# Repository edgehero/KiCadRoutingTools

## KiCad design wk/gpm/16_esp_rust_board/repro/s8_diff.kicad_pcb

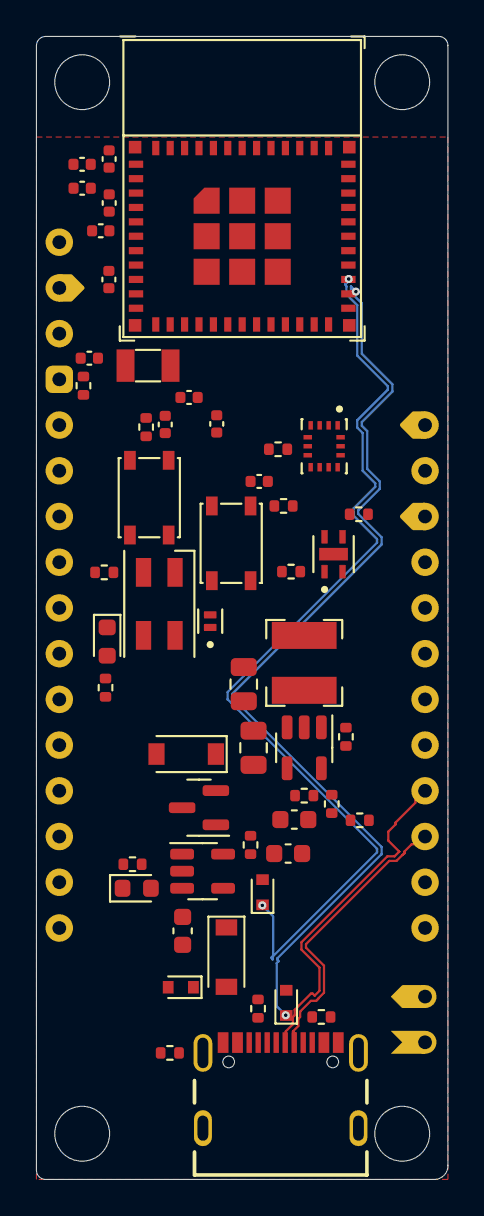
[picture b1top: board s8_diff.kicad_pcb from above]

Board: 2 copper layers, 22.9 x 63.5 mm, 55 parts (1 on the bottom side), 35 nets.

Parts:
C1, C2, C11: 10nF 10V; C_0402_1005Metric
C3, C4, C9: 100nF 10V; C_0402_1005Metric
C5, C7: 10uF 16V; C_0805_2012Metric
C6: 22pF 50V; C_0603_1608Metric
C8, C10: 1uF 16V; C_0402_1005Metric
C12, C13: DNP; C_0402_1005Metric
C14: 1nF 10V; C_0402_1005Metric
C15, C16: 4.7uF 16V; C_0603_1608Metric
D1: LESD8D3.3CAT5G; SOD-882
D2, D3: LED; LED_0603_1608Metric
D4, D6: B5819W; D_SOD-123
D5, D7, D8: LESD5D5.0CT1G; D_SOD-523
D9: WS2812B; LED_SK6812MINI_PLCC4_3.5x3.5mm_P1.75mm
J1: USB4105-GF-A; GCT_USB4105-GF-A
L1: SPH4018H2R2MT (2.2uH 2.2A); L_Bourns-SRN4018
Q1: DMG3415U; SOT-23
R1, R8, R9, R17, R18, R19: 10kR 1%; R_0402_1005Metric
R2, R15: 100kR 1%; R_0402_1005Metric
R3: 22k1R 1%; R_0402_1005Metric
R4, R6: 5k1R 1%; R_0402_1005Metric
R5, R7, R11: 0R 1%; R_0402_1005Metric
R10: 470R 1%; R_0402_1005Metric
R12: DNP; R_0402_1005Metric
R14: 1kR 1%; R_0402_1005Metric
SW1, SW2: SW_Push; SW_SPST_PTS810
TP2: IMU_INT2; TestPoint_Pad_D1.0mm
U1: SHTC3; SON100P200X200X80-5N
U2: ICM-42670-P; IC_ICM-42670-P
U3: ESP32-C3-MINI-1
U4: Rust_Board
U5: SY8088; SOT-23-5
U6: MCP73831T-2ACI/OT; SOT-23-5
Y1: 32.768Hz; Crystal_SMD_3215-2Pin_3.2x1.5mm

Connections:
+3V3: C1.1, C2.1, C3.1, C4.1, C6.1, C7.1, C8.1, C9.1, C11.1, D1.1 (A1), D9.1 (VDD), L1.2, R2.1, R7.2, R8.1, R17.1, R18.1, R19.1, U1.1 (VDD), U2.5 (VDDIO), U2.8 (VDD), U3.3 (3V3), U4.2 (3V3)
+5V: C5.1, D4.1 (K), Q1.2 (S), R1.1, U5.4 (IN)
+BATT: C16.1, Q1.3 (D), U4.28 (VBAT), U4.30 (BAT+), U6.3 (VBAT)
/Buck_Coil: L1.1, U5.3 (LX)
CHIP_PU: C10.1, R8.2, SW1.1, U3.8 (EN/CHIP_PU), U4.1 (RST)
ENABLE: R1.2, U4.27 (ENABLE), U5.1 (EN)
GND: C1.2, C2.2, C3.2, C4.2, C5.2, C7.2, C8.2, C9.2, C10.2, C11.2, C12.2, C13.2, C14.1, C15.1, C16.2, D1.2 (A2), D2.1 (K), D5.2 (A2), D7.2 (A2), D8.2 (A2), D9.3 (VSS), J1.A1_B12 (GND), J1.B1_A12 (GND), R3.2, R4.2, R5.2, R6.2, R9.1, R15.2, SW1.2, SW2.2, U1.4 (VSS), U1.5 (EXP), U2.1 (AP_SDO/AP_AD0), U2.6 (GND), U2.7 (FSYNC), U3.1 (GND), U3.2 (GND), U3.11 (GND), U3.14 (GND), U3.36 (GND), U4.4 (GND), U4.29 (BAT-), U5.2 (GND), U6.2 (VSS)
IO0: C12.1, R12.1, U3.12 (GPIO0/ADC1_CH0/XTAL_32K_P), U4.5 (A0/GPIO0), Y1.1
IO1: C13.1, R12.2, U3.13 (GPIO1/ADC1_CH1/XTAL_32K_N), U4.6 (A1/GPIO1), Y1.2
IO2: R11.1, U3.5 (GPIO2/ADC1_CH2), U4.7 (A2/GPIO2)
IO3: U3.6 (GPIO3/ADC1_CH3), U4.8 (A3/GPIO3)
IO4: U3.18 (GPIO4/ADC1_CH4), U4.9 (A4/GPIO4)
IO5: U3.19 (GPIO5/ADC2_CH0), U4.10 (A5/GPIO5)
IO6: U3.20 (GPIO6), U4.11 (GPIO6)
IO7: R10.1, U3.21 (GPIO7), U4.12 (GPIO7)
IO8_SCL: R17.2, U1.2 (SCL), U2.13 (AP_SCL/AP_SCLK), U3.22 (GPIO8), U4.13 (GPIO8), U4.18 (SCL/GPIO8)
IO9_BOOT: C14.2, R19.2, SW2.1, U3.23 (GPIO9), U4.16 (BOOT/GPIO9)
IO10_SDA: R18.2, U1.3 (SDA), U2.14 (AP_SDA/AP_SDIO/AP_SDI), U3.16 (GPIO10), U4.17 (SDA/GPIO10)
IO20_RX: U3.30 (GPIO20/U0RXD), U4.15 (RXD/GPIO20)
IO21_TX: U3.31 (GPIO21/U0TXD), U4.14 (TXD/GPIO21)
unnamed: C6.2, R2.2, R3.1, U5.5 (FB)
unnamed: D2.2 (A), R10.2
unnamed: D3.1 (K), R14.2
unnamed: D6.2 (A), D7.1 (A1), J1.A4_B9 (VBUS), J1.B4_A9 (VBUS)
unnamed: D9.4 (DIN), R11.2
unnamed: J1.A5 (CC1), R6.1
unnamed: J1.B5 (CC2), R4.1
unnamed: J1.S1 (SHELL_GND), J1.S2 (SHELL_GND), J1.S3 (SHELL_GND), J1.S4 (SHELL_GND), R5.1
unnamed: R7.1, U2.12 (AP_CS)
unnamed: R9.2, U6.5 (PROG)
unnamed: R14.1, U6.1 (STAT)
unnamed: TP2.1, U2.9 (INT2)
USB_D+: D8.1 (A1), J1.A6 (DP1), J1.B6 (DP2), U3.27 (GPIO19/USB_D+), U4.19 (USB_D+/GPIO19)
USB_D-: D5.1 (A1), J1.A7 (DN1), J1.B7 (DN2), U3.26 (GPIO18/USB_D-), U4.20 (USB_D-/GPIO18)
VBUS: C15.2, D3.2 (A), D4.2 (A), D6.1 (K), Q1.1 (G), R15.1, U4.26 (VBUS), U6.4 (VDD)

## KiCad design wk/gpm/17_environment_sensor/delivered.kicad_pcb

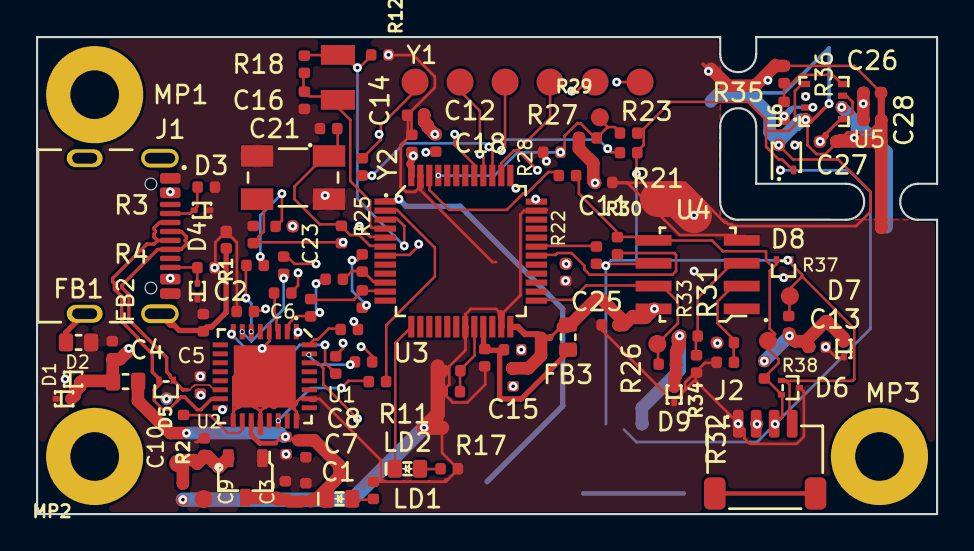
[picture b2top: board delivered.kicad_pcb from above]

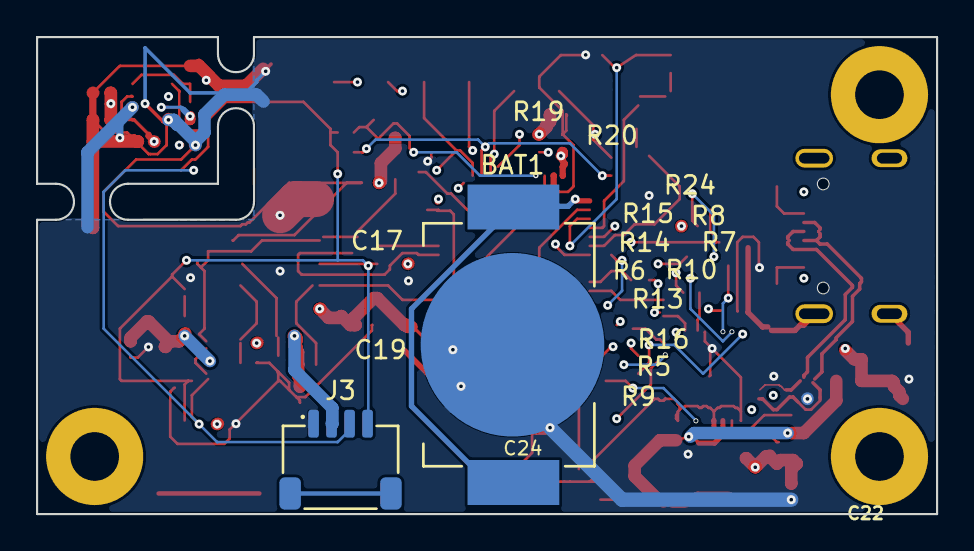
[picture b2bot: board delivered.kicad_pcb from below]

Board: 4 copper layers, 50.0 x 26.5 mm, 107 parts (2 on the bottom side), 50 nets.

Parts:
BAT1: BAT-HLD-012-SMT-TR; BAT_BAT-HLD-012-SMT-TR
C1, C9, C10: C_4u7_0402; C_0402_1005Metric
C2, C3, C5, C6, C8, C12, C13, C15, C17, C18, C19, C22, C25, C26, C27, C28: C_100n_0402; C_0402_1005Metric
C4, C7, C11, C20, C24: C_2u2_0402; C_0402_1005Metric
C14, C16: C_16p_0402; C_0402_1005Metric
C21, C23: C_10p_0402; C_0402_1005Metric
D1, D2, D3, D4, D7, D9: ESD9X5.0ST5G; SOD-923
D5, D6, D8: TPD2E009_SOT-9X3; SOT-723
FB1, FB2, FB3: FB_120Z_2A_Murata-BLM18PG_0603; FB_0603_1608Metric
J1: USB-C_GCT_USB4105-GF-A; USB-C_Receptacle_GCT_USB4105-GF-A
J2, J3: JST_SH_1x4_SM04B-SRSS-TB-LF-SN; Conn_JST_SH_1x4_SM04B-SRSS-TB-LF-SN
LD1, LD2: LED_G_0603_KP-1608ZGC; LED_0603_1608Metric_G
MP1, MP2, MP3: MP_Pad5.4mm_Drill2.7mm
R1, R18, R25: R_1M_0402; R_0402_1005Metric
R2, R26: R_1k_0402; R_0402_1005Metric
R3, R4, R37, R38: R_5k1_0402; R_0402_1005Metric
R5, R6, R7, R8, R9, R10, R11, R13, R14, R15, R16, R20: R_0R_0402; R_0402_1005Metric
R12, R17: R_470R_0402; R_0402_1005Metric
R19, R24, R29, R30, R31, R32, R33, R34, R35, R36: R_100k_0402; R_0402_1005Metric
R21, R22, R23, R27, R28: R_100R_0402; R_0402_1005Metric
TP1, TP2, TP3, TP4, TP5, TP6: TP_1.5mm_SMD; TP_SMD_1.5mm
TP7, TP8, TP9, TP10, TP11, TP12: TP_1mm_SMD; TP_SMD_1mm
U1: FT232R_QFN; QFN-32-1EP_5x5mm
U2: AP7370-33SA-7; SOT-23-3
U3: STM32G474CET6; LQFP-48_7x7mm_P0.5mm
U4: MB85RC1MTPNF-G; SOP-8_3.9x5.05mm_P1.27mm
U5: SHT45; Sensirion_DFN-4-1.5x1.5x0.5mm_P0.8mm
U6: BME280; LGA-8_2.5x2.5mm_BME280
Y1: Resonator_32.768kHz_ECX-31B; Resonator_SMD_ECS_ECX-31B_3.2x1.5x0.9mm
Y2: Resonator_8MHz_ABM3B; Resonator_SMD_Abracon_ABM3B_5x3.2mm

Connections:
+3V3: C9.2, C10.2, C11.1, C12.2, C13.1, C15.2, C17.2, C18.2, C25.1, C26.1, C27.2, C28.1, D7.2 (A), D9.2 (A), FB3.2, J2.2, J3.2, R19.2, R24.2, R26.2, R29.2, R31.2, R33.2, R35.1, R37.2, R38.2, TP9.1, U2.2 (VOUT), U3.24 (VDD), U3.36 (VDD), U3.48 (VDD), U4.8 (VDD), U5.3 (VDD), U6.2 (CSB), U6.6 (VDDIO), U6.8 (VDD)
+5V: C1.2, C3.2, C7.1, C8.1, FB2.2, LD1.1 (C), R2.1, U1.19 (VCC), U2.3 (VIN)
/FRAM_WP: R26.1, TP7.1, U3.25 (PB11), U4.7 (WP)
/FTDI_USER_PB: R11.2, U3.2 (PC13)
/LD2: LD2.1 (C), U3.13 (PA5)
/OSC32_IN: C14.1, R18.1, U3.3 (PC14-OSC32_IN), Y1.1
/OSC32_OUT: C16.1, R18.2, U3.4 (PC15-OSC32_OUT), Y1.2
/USB_CC1: D3.2 (A), J1.A5 (CC_{1}), R3.2
/USB_CC2: D4.2 (A), J1.B5 (CC_{2}), R4.2
/USB_D_N: D5.2, J1.A7 (D_{A}-), J1.B7 (D_{B}-), U1.15 (USBDM)
/USB_D_P: D5.1, J1.A6 (D_{A}+), J1.B6 (D_{B}+), U1.14 (USBDP)
/VBUS: C4.2, D1.2 (A), D2.2 (A), FB2.1, J1.A4 (VBUS), J1.A9 (VBUS), J1.B4 (VBUS), J1.B9 (VBUS)
GND: BAT1.N, C1.1, C2.1, C3.1, C4.1, C5.1, C6.1, C7.2, C8.2, C9.1, C10.1, C11.2, C12.1, C13.2, C14.2, C15.1, C16.2, C17.1, C18.1, C19.2, C20.1, C21.1, C22.2, C23.1, C24.1, C25.2, C26.2, C27.1, C28.2, D1.1 (C), D2.1 (C), D3.1 (C), D4.1 (C), D5.3, D6.3, D7.1 (C), D8.3, D9.1 (C), FB1.2, J1.A1 (GND), J1.A12 (GND), J1.B1 (GND), J1.B12 (GND), J2.1, J3.1, R1.2, R3.1, R4.1, R12.1, R17.1, R30.1, R32.1, R34.1, R36.1, TP10.1, U1.4 (GND), U1.17 (GND), U1.20 (GND), U1.24 (AGND), U1.26 (TEST), U1.33 (EP), U2.1 (GND), U3.19 (VSSA), U3.23 (VSS), U3.35 (VSS), U3.47 (VSS), U4.4 (VSS), U5.4 (VSS), U6.1 (GND), U6.7 (GND), Y2.2 (SH), Y2.4 (SH)
GNDREF: C2.2, FB1.1, J1.SH, R1.1
I2C_1_SCL: D6.1, D8.1, J2.4, J3.4, R22.2, R23.2, R27.2, R37.1, TP12.1, U4.6 (SCL), U5.2 (SCL), U6.4 (SCK)
I2C_1_SDA: D6.2, D8.2, J2.3, J3.3, R21.2, R28.2, R38.1, TP11.1, U4.5 (SDA), U5.1 (SDA), U6.3 (SDI)
JTDI: R10.2, R20.1, TP6.1
JTDO: R9.2, TP5.1, U3.40 (PB3)
JTRST: R7.2, R24.1, TP2.1, U3.41 (PB4)
LPUART_1_STM_RX: R13.2, R16.2, U3.11 (PA3)
LPUART_1_STM_TX: R14.2, R15.2, U3.10 (PA2)
NRST: R8.2, R19.1, TP1.1, U3.7 (PG10-NRST)
unnamed: LD1.2 (A), R12.2
unnamed: LD2.2 (A), R17.2
unnamed: C5.2, C6.2, U1.1 (VCCIO), U1.16 (3V3OUT)
unnamed: R11.1, U1.22 (CBUS0)
unnamed: R9.1, U1.8 (CTS#)
unnamed: R8.1, U1.7 (DCD#)
unnamed: R7.1, U1.6 (DSR#)
unnamed: R5.1, U1.31 (DTR#)
unnamed: R2.2, U1.18 (RESET#)
unnamed: R10.1, U1.3 (RI#)
unnamed: R6.1, U1.32 (RTS#)
unnamed: R14.1, R16.1, U1.2 (RXD)
unnamed: R13.1, R15.1, U1.30 (TXD)
unnamed: R21.1, U3.30 (PA8)
unnamed: R22.1, U3.31 (PA9)
unnamed: R20.2, R23.1, U3.39 (PA15)
unnamed: R27.1, R29.1, R30.2, TP8.1, U3.45 (PB8-BOOT0)
unnamed: R28.1, U3.46 (PB9)
unnamed: C23.2, R25.2, U3.5 (PF0-OSC_IN), Y2.3
unnamed: C21.2, R25.1, U3.6 (PF1-OSC_OUT), Y2.1
unnamed: BAT1.P1, BAT1.P2, U3.1 (VBAT)
unnamed: C19.1, C20.2, FB3.1, U3.21 (VDDA)
unnamed: C22.1, C24.2, U3.20 (VREF+)
unnamed: R31.1, R32.2, U4.2 (A1)
unnamed: R33.1, R34.2, U4.3 (A2)
unnamed: R35.2, R36.2, U6.5 (SDO)
SWCLK-JTCK: R6.2, TP4.1, U3.38 (PA14)
SWDIO-JTMS: R5.2, TP3.1, U3.37 (PA13)

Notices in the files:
parts and their libraries:
License: Apache-2.0
